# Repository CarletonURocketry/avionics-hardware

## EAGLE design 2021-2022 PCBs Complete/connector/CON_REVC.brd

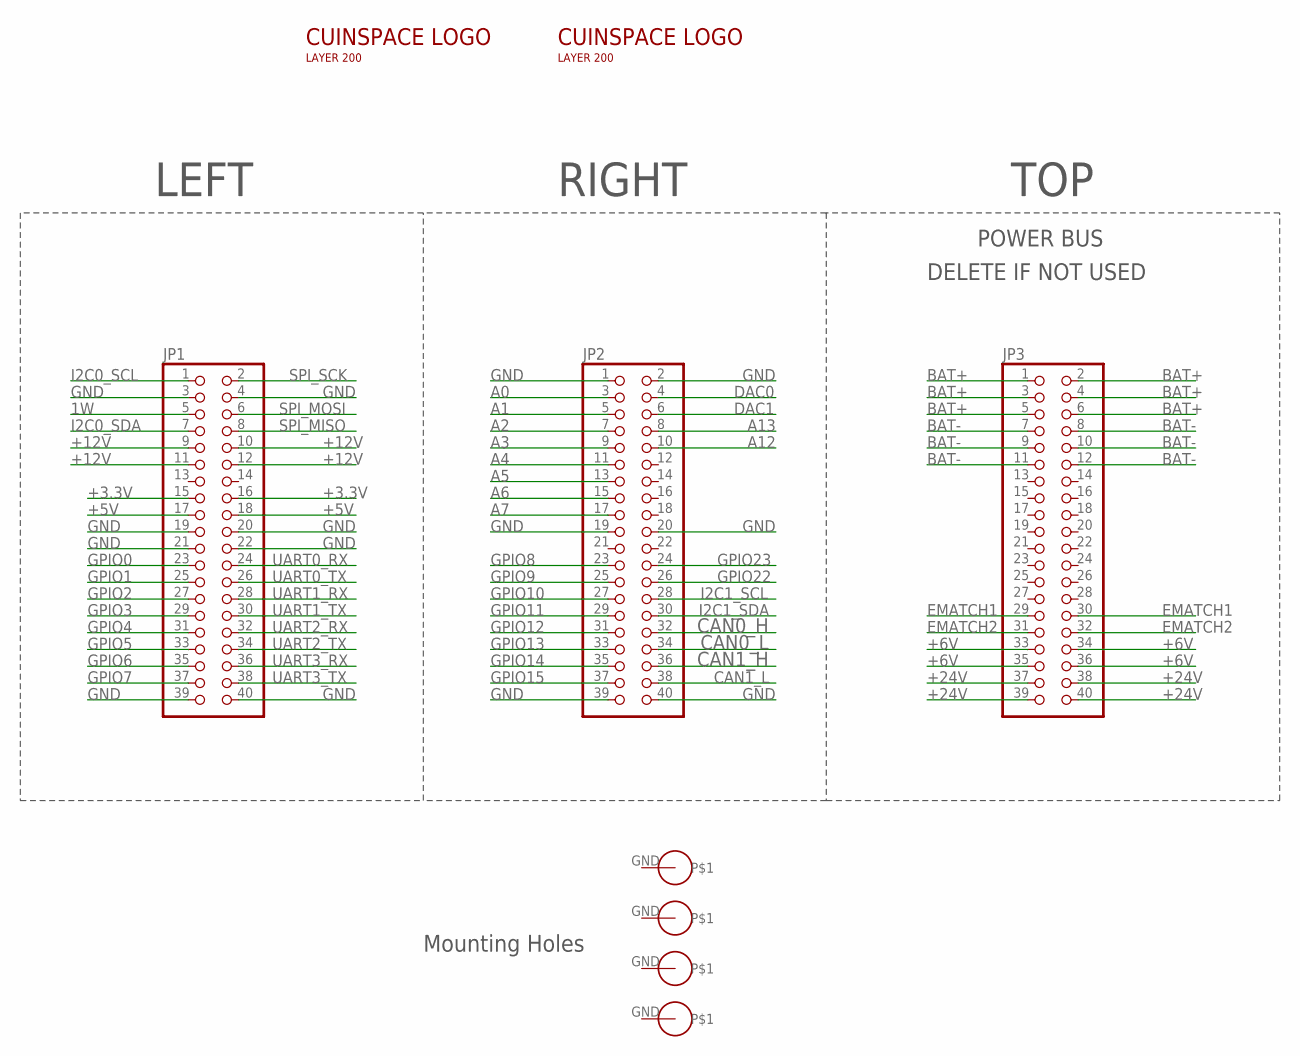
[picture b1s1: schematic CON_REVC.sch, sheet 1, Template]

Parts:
$$U$1: PS/104-MOUNTING-HOLE; PC/104-MOUNTING-HOLE
JP1, JP2, JP3: PINHD-2X20; 2X20
U$1, U$2, U$3: PS/104-MOUNTING-HOLE; PC/104-MOUNTING-HOLE
U$5, U$6: INSPACE3CM_L; INSPACE_3CM_LETTERS

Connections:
1W: JP1.5
+3.3V: JP1.15, JP1.16
+5V: JP1.17, JP1.18; also elsewhere on the board
+6V: JP3.33, JP3.34, JP3.35, JP3.36
+12V: JP1.9, JP1.10, JP1.11, JP1.12
+24V: JP3.37, JP3.38, JP3.39, JP3.40
A0: JP2.3
A1: JP2.5
A2: JP2.7
A3: JP2.9
A4: JP2.11
A5: JP2.13
A6: JP2.15
A7: JP2.17
A12: JP2.10
A13: JP2.8
BAT+: JP3.1, JP3.2, JP3.3, JP3.4, JP3.5, JP3.6; also elsewhere on the board
BAT-: JP3.7, JP3.8, JP3.9, JP3.10, JP3.11, JP3.12; also elsewhere on the board
CAN0_H: JP2.32; also elsewhere on the board
CAN0_L: JP2.34; also elsewhere on the board
CAN1_H: JP2.36; also elsewhere on the board
CAN1_L: JP2.38; also elsewhere on the board
DAC0: JP2.4
DAC1: JP2.6
EMATCH1: JP3.29, JP3.30; also elsewhere on the board
EMATCH2: JP3.31, JP3.32; also elsewhere on the board
GND: JP1.3, JP1.4, JP1.19, JP1.20, JP1.21, JP1.22, JP1.39, JP1.40, JP2.1, JP2.2, JP2.19, JP2.20, JP2.39, JP2.40; also elsewhere on the board
GPIO0: JP1.23
GPIO1: JP1.25
GPIO2: JP1.27
GPIO3: JP1.29
GPIO4: JP1.31
GPIO5: JP1.33
GPIO6: JP1.35
GPIO7: JP1.37
GPIO8: JP2.23
GPIO9: JP2.25
GPIO10: JP2.27
GPIO11: JP2.29
GPIO12: JP2.31
GPIO13: JP2.33
GPIO14: JP2.35
GPIO15: JP2.37; also elsewhere on the board
GPIO22: JP2.26
GPIO23: JP2.24
I2C0_SCL: JP1.1
I2C0_SDA: JP1.7
I2C1_SCL: JP2.28
I2C1_SDA: JP2.30
SPI_MISO: JP1.8
SPI_MOSI: JP1.6
SPI_SCK: JP1.2
UART0_RX: JP1.24
UART0_TX: JP1.26
UART1_RX: JP1.28
UART1_TX: JP1.30
UART2_RX: JP1.32
UART2_TX: JP1.34
UART3_RX: JP1.36
UART3_TX: JP1.38

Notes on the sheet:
POWER BUS
DELETE IF NOT USED
LEFT
RIGHT
TOP
Mounting Holes

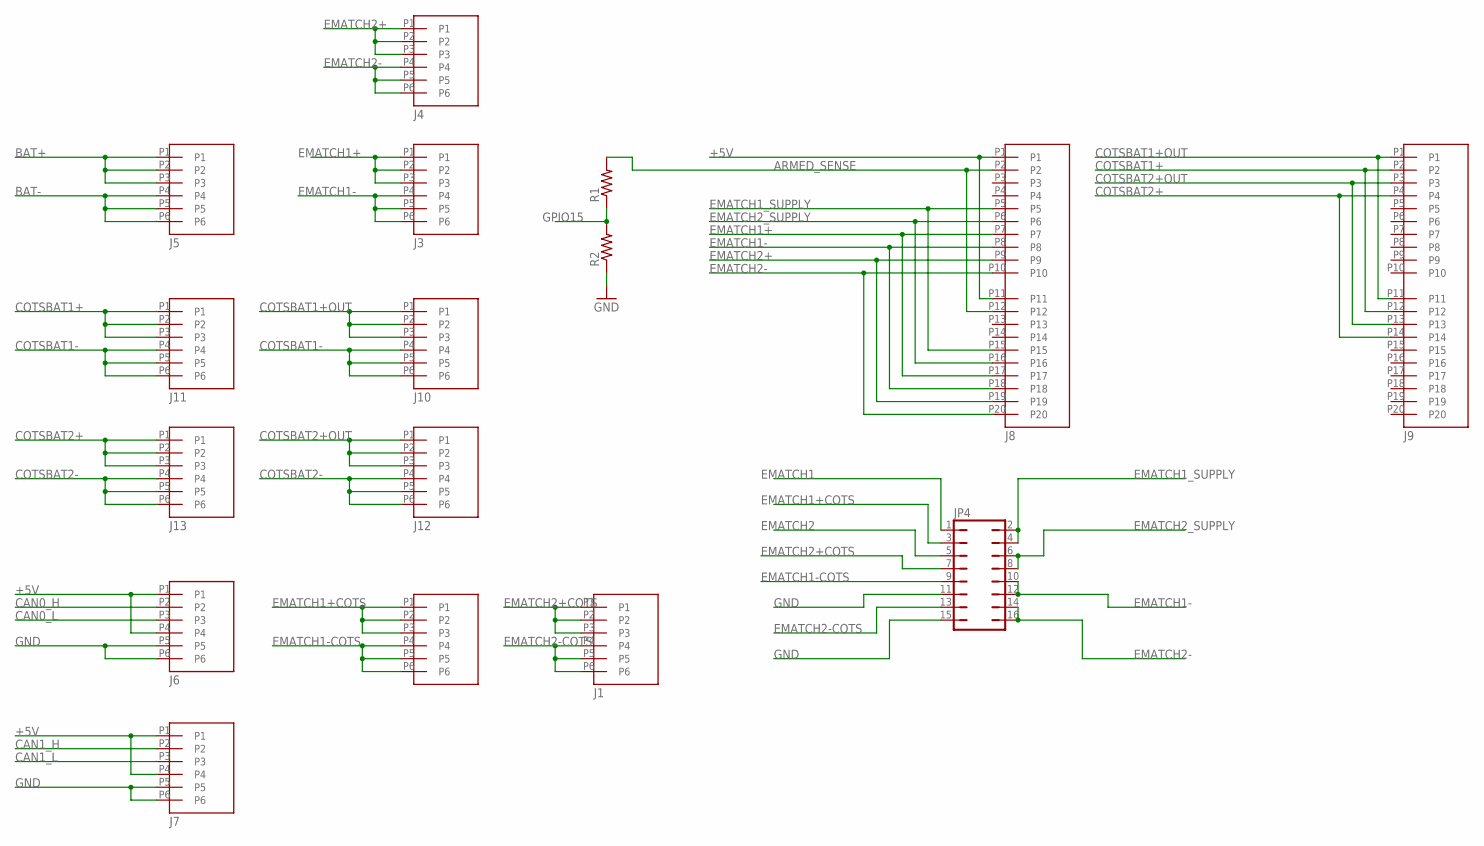
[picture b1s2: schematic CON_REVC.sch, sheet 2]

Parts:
J1, J2, J3, J4, J5, J6, J7, J10, J11, J12, J13: M80-5100642
J8, J9: M80-5102042
JP4: JP8Q
R1, R2: R-US_R0805; R0805

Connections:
+5V: J6.P1, J6.P4, J7.P1, J7.P4, J8.P1, J8.P11; also elsewhere on the board
ARMED_SENSE: J8.P2, J8.P12, R1.2
BAT+: J5.P1, J5.P2, J5.P3; also elsewhere on the board
BAT-: J5.P4, J5.P5, J5.P6; also elsewhere on the board
CAN0_H: J6.P2; also elsewhere on the board
CAN0_L: J6.P3; also elsewhere on the board
CAN1_H: J7.P2; also elsewhere on the board
CAN1_L: J7.P3; also elsewhere on the board
COTSBAT1+: J9.P2, J9.P12, J11.P1, J11.P2, J11.P3
COTSBAT1+OUT: J9.P1, J9.P11, J10.P1, J10.P2, J10.P3
COTSBAT1-: J10.P4, J10.P5, J10.P6, J11.P4, J11.P5, J11.P6
COTSBAT2+: J9.P4, J9.P14, J13.P1, J13.P2, J13.P3
COTSBAT2+OUT: J9.P3, J9.P13, J12.P1, J12.P2, J12.P3
COTSBAT2-: J12.P4, J12.P5, J12.P6, J13.P4, J13.P5, J13.P6
EMATCH1: JP4.1; also elsewhere on the board
EMATCH1+: J3.P1, J3.P2, J3.P3, J8.P7, J8.P17
EMATCH1+COTS: J2.P1, J2.P2, J2.P3, JP4.3
EMATCH1-: J3.P4, J3.P5, J3.P6, J8.P8, J8.P18, JP4.10, JP4.12
EMATCH1-COTS: J2.P4, J2.P5, J2.P6, JP4.9
EMATCH1_SUPPLY: J8.P5, J8.P15, JP4.2, JP4.4
EMATCH2: JP4.5; also elsewhere on the board
EMATCH2+: J4.P1, J4.P2, J4.P3, J8.P9, J8.P19
EMATCH2+COTS: J1.P1, J1.P2, J1.P3, JP4.7
EMATCH2-: J4.P4, J4.P5, J4.P6, J8.P10, J8.P20, JP4.14, JP4.16
EMATCH2-COTS: J1.P4, J1.P5, J1.P6, JP4.13
EMATCH2_SUPPLY: J8.P6, J8.P16, JP4.6, JP4.8
GND: J6.P5, J6.P6, J7.P5, J7.P6, JP4.11, JP4.15, R2.1; also elsewhere on the board
GPIO15: R1.1, R2.2; also elsewhere on the board

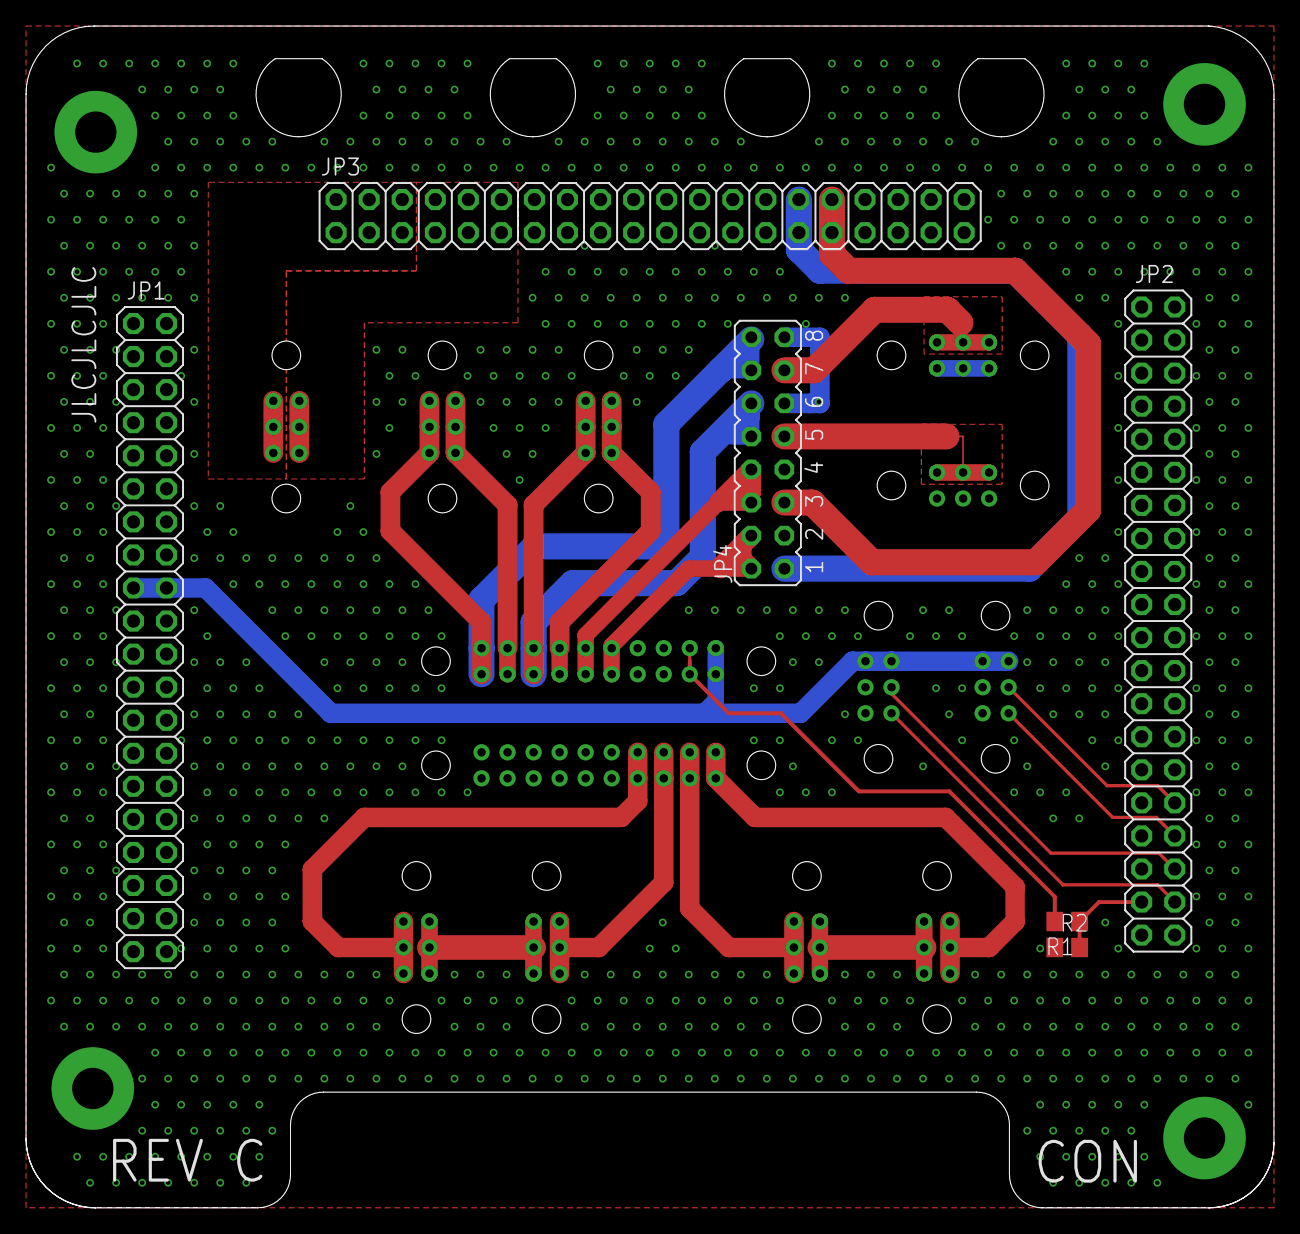
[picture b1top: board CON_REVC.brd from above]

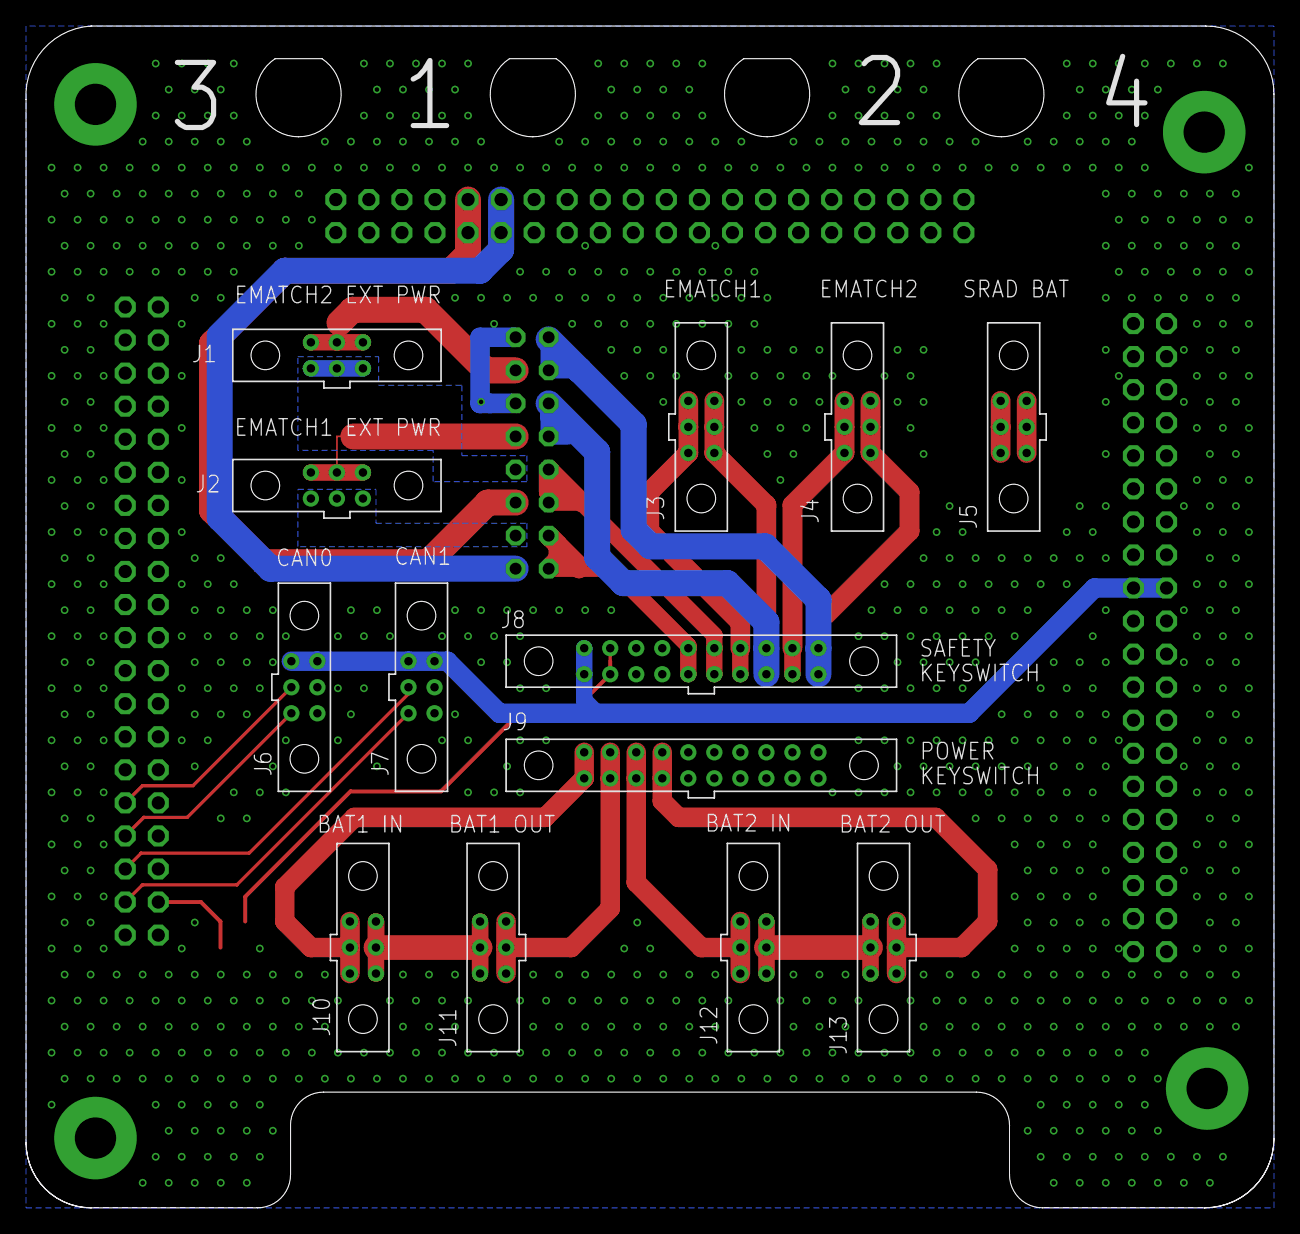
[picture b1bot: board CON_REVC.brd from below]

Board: 2 copper layers, 95.9 x 90.8 mm, 25 parts (15 on the bottom side), 32 nets.

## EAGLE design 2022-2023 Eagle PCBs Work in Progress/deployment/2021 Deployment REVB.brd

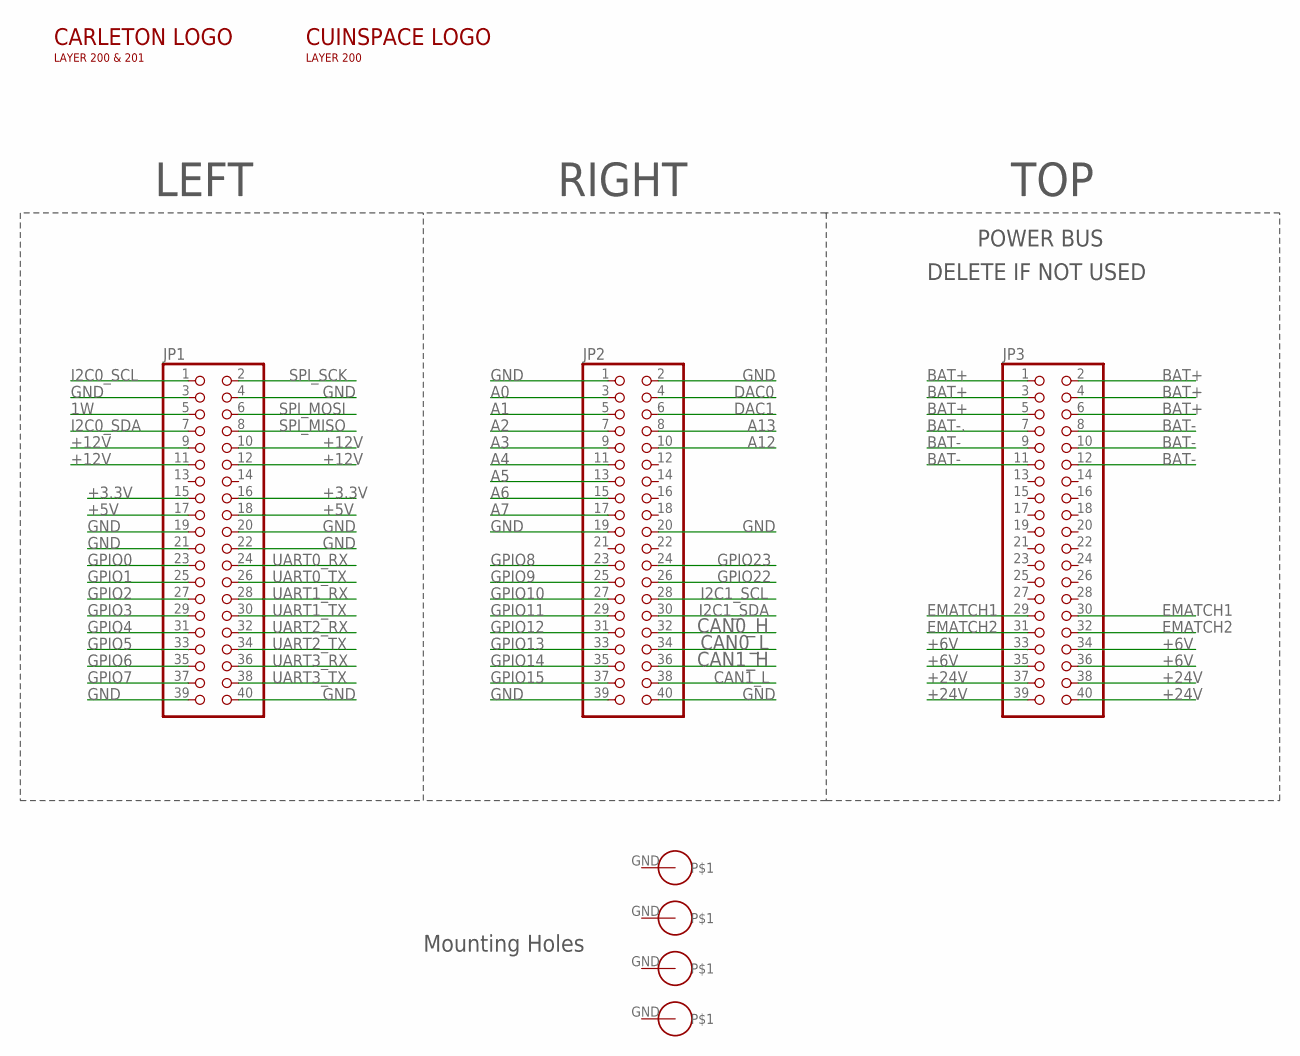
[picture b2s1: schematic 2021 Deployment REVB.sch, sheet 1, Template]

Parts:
$$U$1: PS/104-MOUNTING-HOLE; PC/104-MOUNTING-HOLE
JP1, JP2, JP3: PINHD-2X20; 2X20
U$1, U$2, U$3: PS/104-MOUNTING-HOLE; PC/104-MOUNTING-HOLE
U$4: CARLETON3CM; CARLETONU_3CM
U$6: INSPACE3CM_L; INSPACE_3CM_LETTERS

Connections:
1W: JP1.5
+3.3V: JP1.15, JP1.16
+5V: JP1.17, JP1.18
+6V: JP3.33, JP3.34, JP3.35, JP3.36
+12V: JP1.9, JP1.10, JP1.11, JP1.12
+24V: JP3.37, JP3.38, JP3.39, JP3.40
A0: JP2.3
A1: JP2.5
A2: JP2.7
A3: JP2.9
A4: JP2.11
A5: JP2.13
A6: JP2.15
A7: JP2.17
A12: JP2.10
A13: JP2.8
BAT+: JP3.1, JP3.2, JP3.3, JP3.4, JP3.5, JP3.6
BAT-: JP3.8, JP3.9, JP3.10, JP3.11, JP3.12
BAT-.: JP3.7
CAN0_H: JP2.32
CAN0_L: JP2.34
CAN1_H: JP2.36
CAN1_L: JP2.38
DAC0: JP2.4
DAC1: JP2.6
EMATCH1: JP3.29, JP3.30
EMATCH2: JP3.31, JP3.32
GND: JP1.3, JP1.4, JP1.19, JP1.20, JP1.21, JP1.22, JP1.39, JP1.40, JP2.1, JP2.2, JP2.19, JP2.20, JP2.39, JP2.40
GPIO0: JP1.23
GPIO1: JP1.25
GPIO2: JP1.27
GPIO3: JP1.29
GPIO4: JP1.31
GPIO5: JP1.33
GPIO6: JP1.35
GPIO7: JP1.37
GPIO8: JP2.23
GPIO9: JP2.25
GPIO10: JP2.27
GPIO11: JP2.29
GPIO12: JP2.31
GPIO13: JP2.33
GPIO14: JP2.35
GPIO15: JP2.37
GPIO22: JP2.26
GPIO23: JP2.24
I2C0_SCL: JP1.1
I2C0_SDA: JP1.7
I2C1_SCL: JP2.28
I2C1_SDA: JP2.30
SPI_MISO: JP1.8
SPI_MOSI: JP1.6
SPI_SCK: JP1.2
UART0_RX: JP1.24
UART0_TX: JP1.26
UART1_RX: JP1.28
UART1_TX: JP1.30
UART2_RX: JP1.32
UART2_TX: JP1.34
UART3_RX: JP1.36
UART3_TX: JP1.38

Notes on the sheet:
POWER BUS
DELETE IF NOT USED
LEFT
RIGHT
TOP
Mounting Holes

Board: 2 copper layers, 9 parts (0 on the bottom side), 10 nets, no tracks yet.

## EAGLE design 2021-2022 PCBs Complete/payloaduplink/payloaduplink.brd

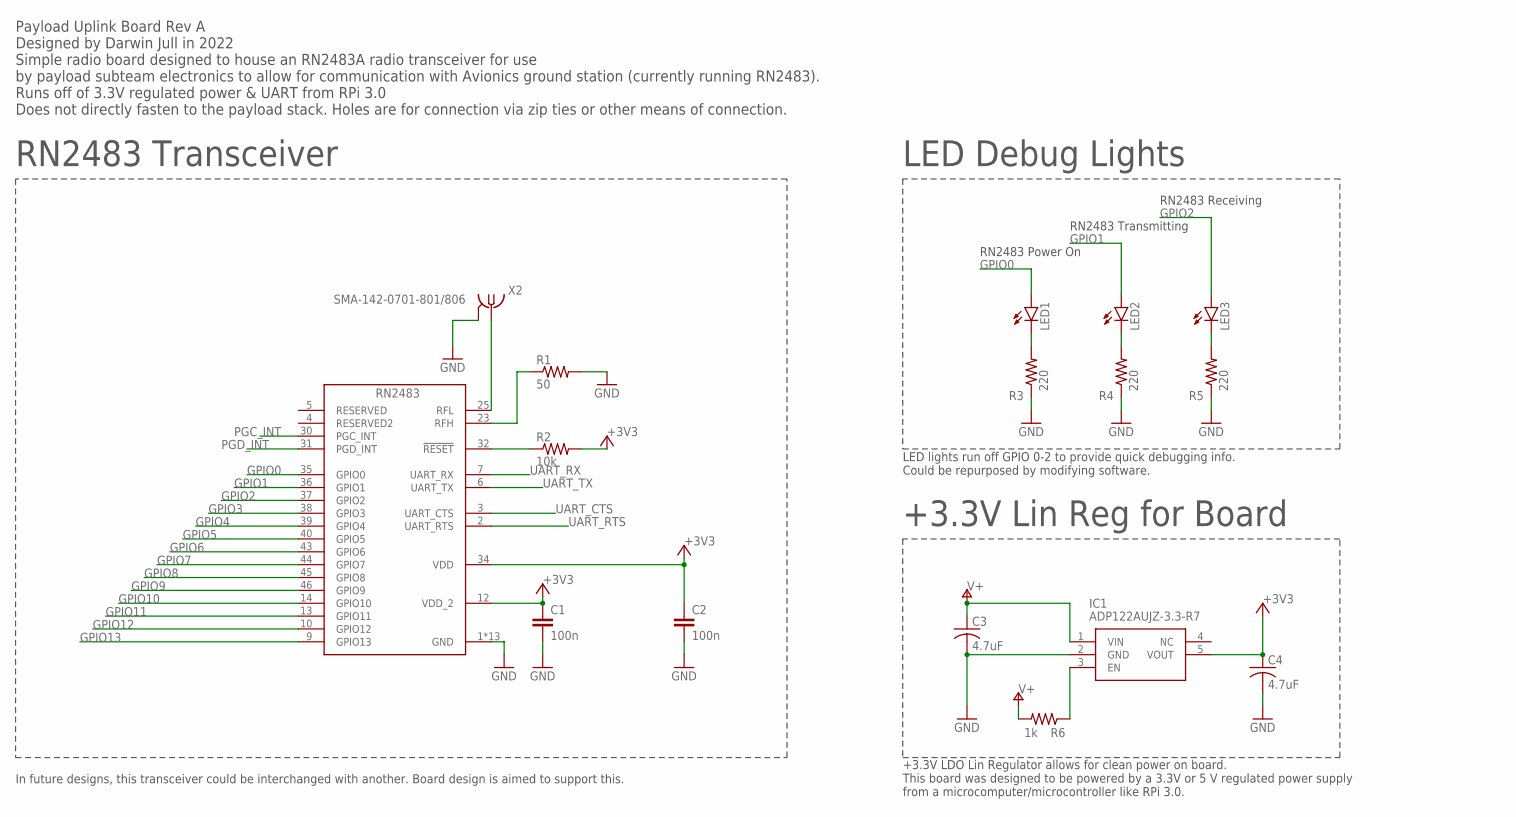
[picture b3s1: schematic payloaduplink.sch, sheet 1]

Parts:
C1, C2: 100n; C0805
C3, C4: 4.7uF; C0805
IC1: ADP122AUJZ-3.3-R7; SOT95P280X100-5N
LED1, LED2, LED3: LEDCHIPLED_0603; CHIPLED_0603
R1: 50; R0402
R2: 10k; R0805
R3, R4, R5: 220; R0805
R6: 1k; R0805
U$1: RN2483_TRANSCIEVER; RN2483
X2: SMA-142-0701-801/806; J502-ND-142-0701-801/806

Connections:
+3V3: C1.1, C2.1, C4.1, IC1.5 (VOUT), R2.2, U$1.12 (VDD_2), U$1.34 (VDD)
GND: C1.2, C2.2, C3.2, C4.2, IC1.2 (GND), R1.2, R3.1, R4.1, R5.1, U$1.1 (GND), U$1.8 (GND), U$1.11 (GND), U$1.20 (GND), U$1.21 (GND), U$1.22 (GND), U$1.24 (GND), U$1.26 (GND), U$1.27 (GND), U$1.28 (GND), U$1.33 (GND), U$1.41 (GND), U$1.47 (GND), X2.G@1 (2), X2.G@2 (2), X2.G@3 (2), X2.G@4 (2); also elsewhere on the board
GPIO0: LED1.A, U$1.35 (GPIO0)
GPIO1: LED2.A, U$1.36 (GPIO1)
GPIO2: LED3.A, U$1.37 (GPIO2)
GPIO3: U$1.38 (GPIO3); also elsewhere on the board
GPIO4: U$1.39 (GPIO4); also elsewhere on the board
GPIO5: U$1.40 (GPIO5); also elsewhere on the board
GPIO6: U$1.43 (GPIO6); also elsewhere on the board
GPIO7: U$1.44 (GPIO7); also elsewhere on the board
GPIO8: U$1.45 (GPIO8); also elsewhere on the board
GPIO9: U$1.46 (GPIO9); also elsewhere on the board
GPIO10: U$1.14 (GPIO10); also elsewhere on the board
GPIO11: U$1.13 (GPIO11); also elsewhere on the board
GPIO12: U$1.10 (GPIO12); also elsewhere on the board
GPIO13: U$1.9 (GPIO13); also elsewhere on the board
unnamed: U$1.25 (RFL), X2.1
unnamed: R1.1, U$1.23 (RFH)
unnamed: LED1.C, R3.2
unnamed: LED2.C, R4.2
unnamed: LED3.C, R5.2
unnamed: R2.1, U$1.32 (!RESET)
unnamed: IC1.3 (EN), R6.1
PGC_INT: U$1.30 (PGC_INT); also elsewhere on the board
PGD_INT: U$1.31 (PGD_INT); also elsewhere on the board
UART_CTS: U$1.3 (UART_CTS); also elsewhere on the board
UART_RTS: U$1.2 (UART_RTS); also elsewhere on the board
UART_RX: U$1.7 (UART_RX); also elsewhere on the board
UART_TX: U$1.6 (UART_TX); also elsewhere on the board
V+: C3.1, IC1.1 (VIN), R6.2; also elsewhere on the board

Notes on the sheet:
RN2483 Transceiver
LED Debug Lights
+3.3V Lin Reg for Board
In future designs, this transceiver could be interchanged with another. Board design is aimed to support this.
+3.3V LDO Lin Regulator allows for clean power on board. This board was designed to be powered by a 3.3V or 5 V regulated power supply from a microcomputer/microcontroller like RPi 3.0.
LED lights run off GPIO 0-2 to provide quick debugging info. Could be repurposed by modifying software.
Payload Uplink Board Rev A Designed by Darwin Jull in 2022 Simple radio board designed to house an RN2483A radio transceiver for use by payload subteam electronics to allow for communication with Avionics ground station (currently running RN2483). Runs off of 3.3V regulated power & UART from RPi 3.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
RN2483 Power On
RN2483 Transmitting
RN2483 Receiving

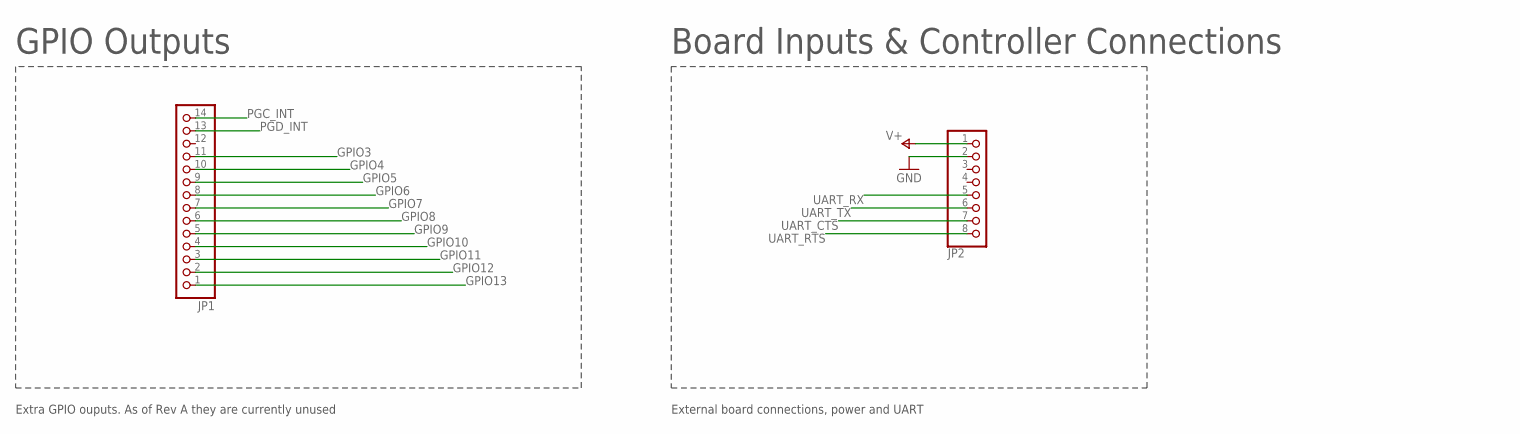
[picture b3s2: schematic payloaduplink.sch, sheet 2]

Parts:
JP1: PINHD-1X14; 1X14
JP2: PINHD-1X8; 1X08

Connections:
GND: JP2.2; also elsewhere on the board
GPIO3: JP1.11; also elsewhere on the board
GPIO4: JP1.10; also elsewhere on the board
GPIO5: JP1.9; also elsewhere on the board
GPIO6: JP1.8; also elsewhere on the board
GPIO7: JP1.7; also elsewhere on the board
GPIO8: JP1.6; also elsewhere on the board
GPIO9: JP1.5; also elsewhere on the board
GPIO10: JP1.4; also elsewhere on the board
GPIO11: JP1.3; also elsewhere on the board
GPIO12: JP1.2; also elsewhere on the board
GPIO13: JP1.1; also elsewhere on the board
PGC_INT: JP1.14; also elsewhere on the board
PGD_INT: JP1.13; also elsewhere on the board
UART_CTS: JP2.7; also elsewhere on the board
UART_RTS: JP2.8; also elsewhere on the board
UART_RX: JP2.5; also elsewhere on the board
UART_TX: JP2.6; also elsewhere on the board
V+: JP2.1; also elsewhere on the board

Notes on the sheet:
GPIO Outputs
Board Inputs & Controller Connections
External board connections, power and UART
Extra GPIO ouputs. As of Rev A they are currently unused

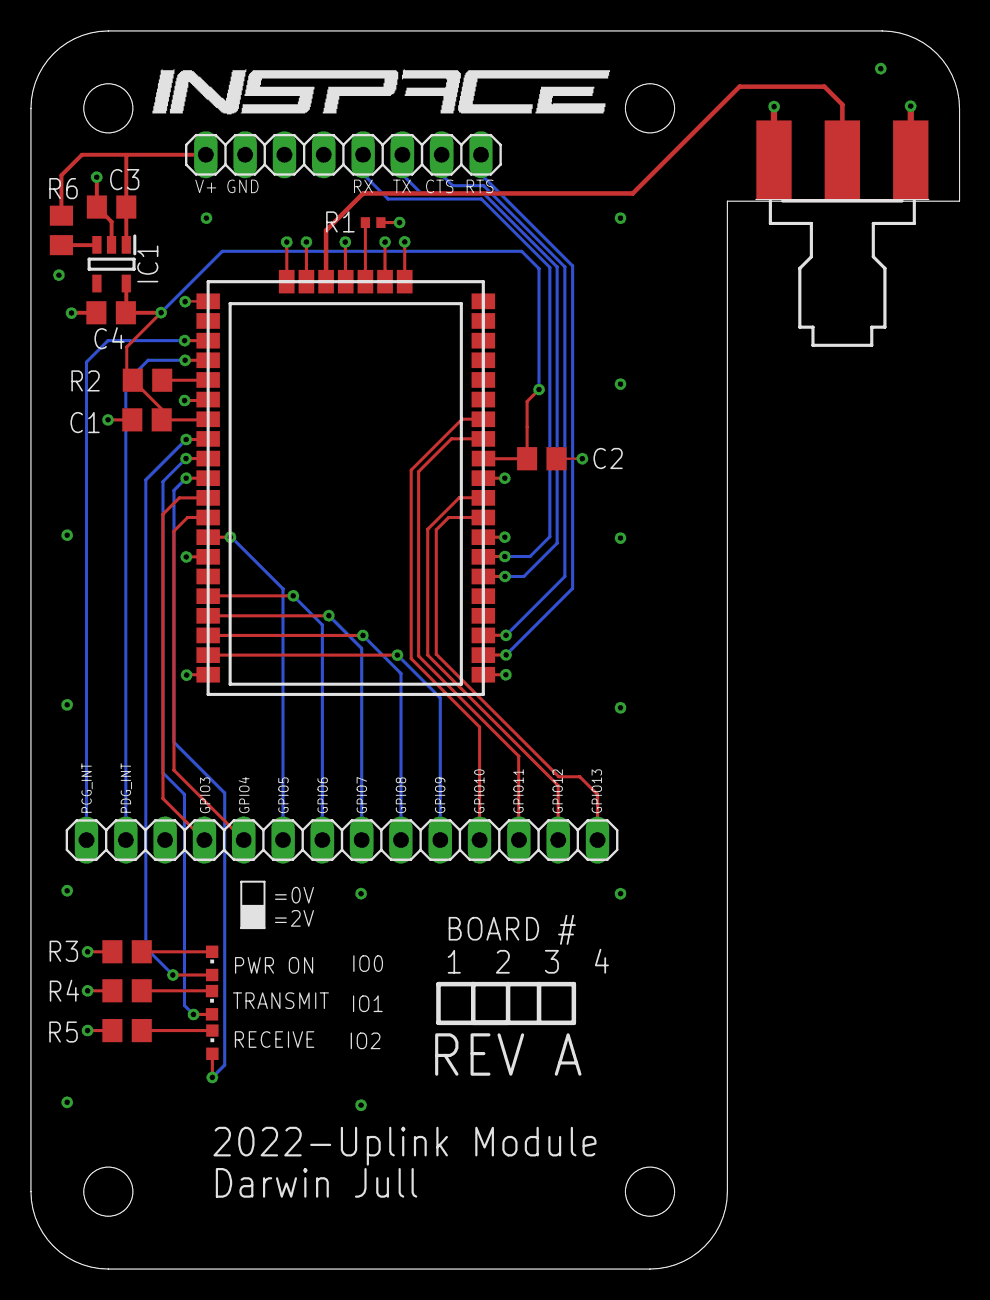
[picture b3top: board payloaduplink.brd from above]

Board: 4 copper layers, 60.0 x 80.0 mm, 19 parts (0 on the bottom side), 30 nets.

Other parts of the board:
U$2: INSPACE_3CM_LETTERS

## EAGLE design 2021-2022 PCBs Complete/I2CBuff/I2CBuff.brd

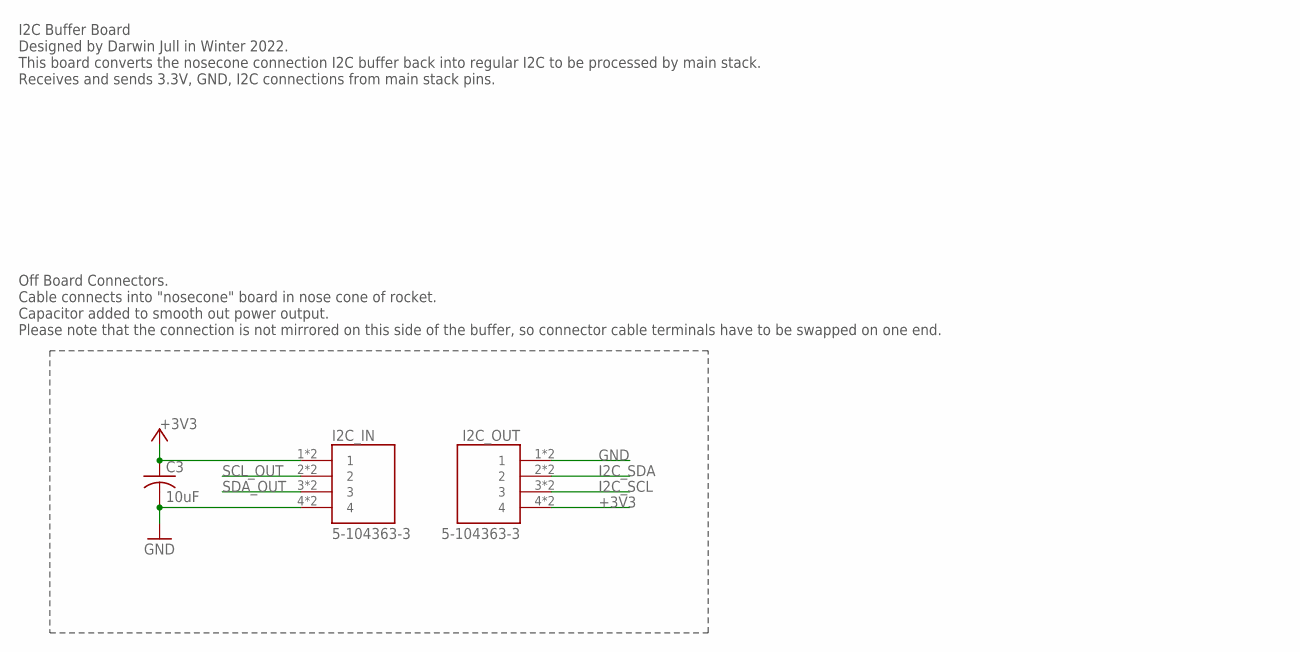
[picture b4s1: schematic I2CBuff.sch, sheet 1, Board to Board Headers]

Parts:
C3: 10uF; C0805
I2C_IN, I2C_OUT: 5-104363-3; TE_5-104363-3

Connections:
+3V3: C3.1, I2C_IN.1, I2C_IN.1_1 (1), I2C_OUT.4, I2C_OUT.4_1 (4); also elsewhere on the board
GND: C3.2, I2C_IN.4, I2C_IN.4_1 (4), I2C_OUT.1, I2C_OUT.1_1 (1); also elsewhere on the board
I2C_SCL: I2C_OUT.3, I2C_OUT.3_1 (3); also elsewhere on the board
I2C_SDA: I2C_OUT.2, I2C_OUT.2_1 (2); also elsewhere on the board
SCL_OUT: I2C_IN.2, I2C_IN.2_1 (2); also elsewhere on the board
SDA_OUT: I2C_IN.3, I2C_IN.3_1 (3); also elsewhere on the board

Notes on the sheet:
I2C Buffer Board Designed by Darwin Jull in Winter 2022. This board converts the nosecone connection I2C buffer back into regular I2C to be processed by main stack. Receives and sends 3.3V, GND, I2C connections from main stack pins.
Off Board Connectors. Cable connects into "nosecone" board in nose cone of rocket. Capacitor added to smooth out power output. Please note that the connection is not mirrored on this side of the buffer, so connector cable terminals have to be swapped on one end.

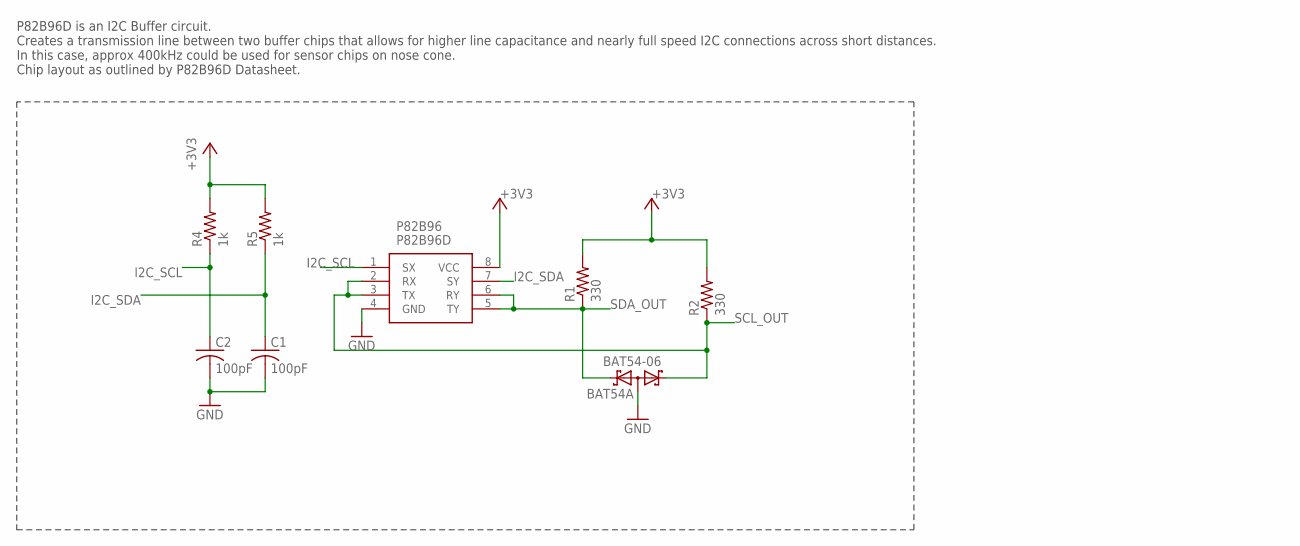
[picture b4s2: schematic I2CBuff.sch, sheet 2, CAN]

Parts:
C1, C2: 100pF; C0805
D1: BAT54-06; SOT23
P82B96: P82B96D; SOIC127P600X175-8N
R1, R2: 330; R0805
R4, R5: 1k; R0805

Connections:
+3V3: P82B96.8 (VCC), R1.2, R2.2, R4.2, R5.2; also elsewhere on the board
GND: C1.2, C2.2, D1.3, P82B96.4 (GND); also elsewhere on the board
I2C_SCL: C2.1, P82B96.1 (SX), R4.1; also elsewhere on the board
I2C_SDA: C1.1, P82B96.7 (SY), R5.1; also elsewhere on the board
SCL_OUT: D1.1, P82B96.2 (RX), P82B96.3 (TX), R2.1; also elsewhere on the board
SDA_OUT: D1.2, P82B96.5 (TY), P82B96.6 (RY), R1.1; also elsewhere on the board

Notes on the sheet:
P82B96D is an I2C Buffer circuit. Creates a transmission line between two buffer chips that allows for higher line capacitance and nearly full speed I2C connections across short distances. In this case, approx 400kHz could be used for sensor chips on nose cone. Chip layout as outlined by P82B96D Da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

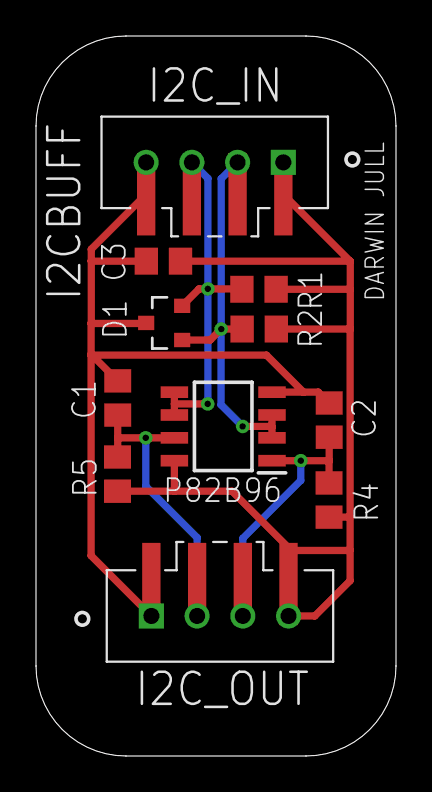
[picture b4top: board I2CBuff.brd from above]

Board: 2 copper layers, 20.0 x 40.0 mm, 11 parts (0 on the bottom side), 6 nets.

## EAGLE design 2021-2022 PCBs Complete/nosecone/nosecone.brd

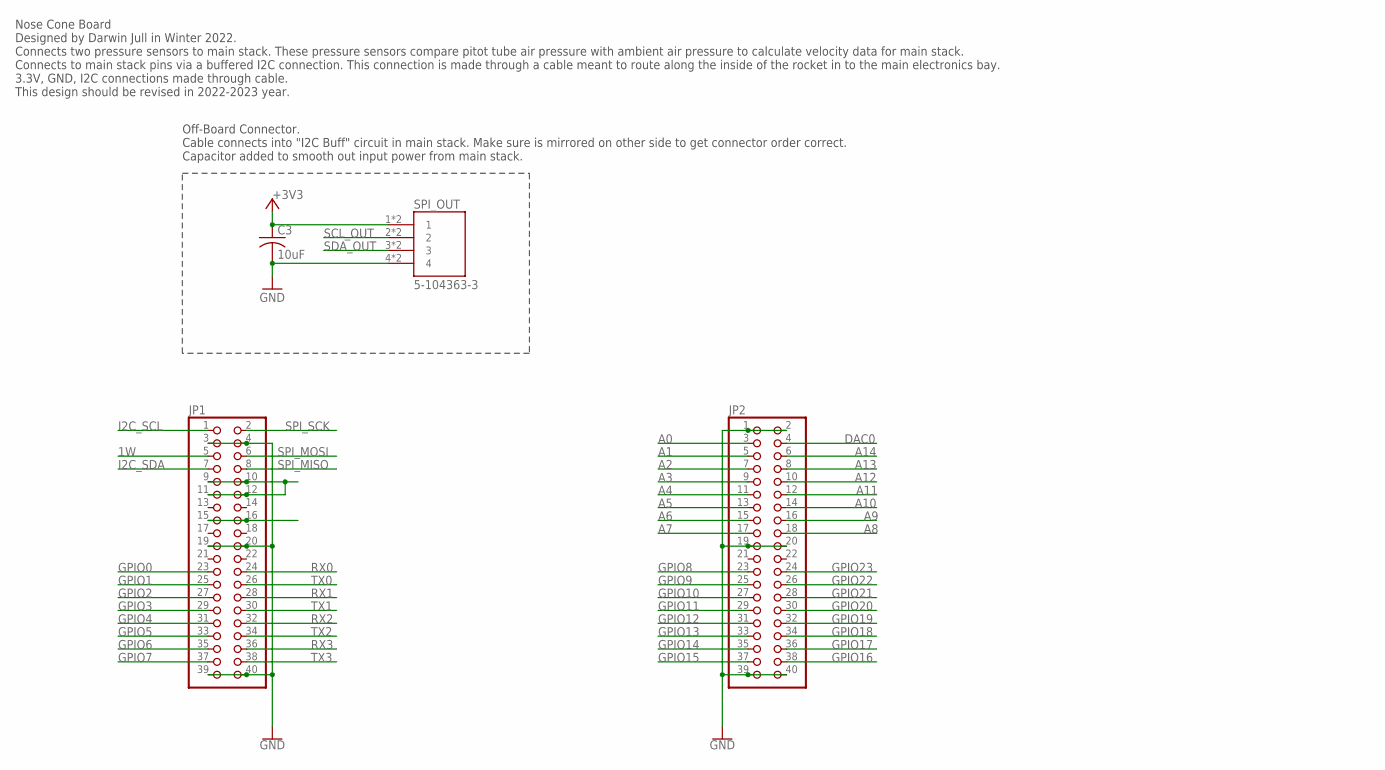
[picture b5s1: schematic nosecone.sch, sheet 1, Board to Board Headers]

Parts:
C3: 10uF; C0805
JP1, JP2: PINHD-2X20; 2X20
SPI_OUT: 5-104363-3; TE_5-104363-3

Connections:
1W: JP1.5
+3V3: C3.1, SPI_OUT.1, SPI_OUT.1_1 (1); also elsewhere on the board
A0: JP2.3
A1: JP2.5
A2: JP2.7
A3: JP2.9
A4: JP2.11
A5: JP2.13
A6: JP2.15
A7: JP2.17
A8: JP2.18
A9: JP2.16
A10: JP2.14
A11: JP2.12
A12: JP2.10
A13: JP2.8
A14: JP2.6
DAC0: JP2.4
GND: C3.2, JP1.3, JP1.4, JP1.19, JP1.20, JP1.39, JP1.40, JP2.1, JP2.2, JP2.19, JP2.20, JP2.39, JP2.40, SPI_OUT.4, SPI_OUT.4_1 (4); also elsewhere on the board
GPIO0: JP1.23
GPIO1: JP1.25
GPIO2: JP1.27
GPIO3: JP1.29
GPIO4: JP1.31
GPIO5: JP1.33
GPIO6: JP1.35
GPIO7: JP1.37
GPIO8: JP2.23
GPIO9: JP2.25
GPIO10: JP2.27
GPIO11: JP2.29
GPIO12: JP2.31
GPIO13: JP2.33
GPIO14: JP2.35
GPIO15: JP2.37
GPIO16: JP2.38
GPIO17: JP2.36
GPIO18: JP2.34
GPIO19: JP2.32
GPIO20: JP2.30
GPIO21: JP2.28
GPIO22: JP2.26
GPIO23: JP2.24
I2C_SCL: JP1.1; also elsewhere on the board
I2C_SDA: JP1.7; also elsewhere on the board
unnamed: JP1.9, JP1.10, JP1.11, JP1.12
unnamed: JP1.15, JP1.16
RX0: JP1.24
RX1: JP1.28
RX2: JP1.32
RX3: JP1.36
SCL_OUT: SPI_OUT.2, SPI_OUT.2_1 (2); also elsewhere on the board
SDA_OUT: SPI_OUT.3, SPI_OUT.3_1 (3); also elsewhere on the board
SPI_MISO: JP1.8
SPI_MOSI: JP1.6
SPI_SCK: JP1.2
TX0: JP1.26
TX1: JP1.30
TX2: JP1.34
TX3: JP1.38

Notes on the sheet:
Off-Board Connector. Cable connects into "I2C Buff" circuit in main stack. Make sure is mirrored on other side to get connector order correct. Capacitor added to smooth out input power from main stack.
Nose Cone Board Designed by Darwin Jull in Winter 2022. Connects two pressure sensors to main stack. These pressure sensors compare pitot tube air pressure with ambient air pressure to calculate velocity data for main stack. Connects to main stack pins via a buffered I2C connection. This connection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

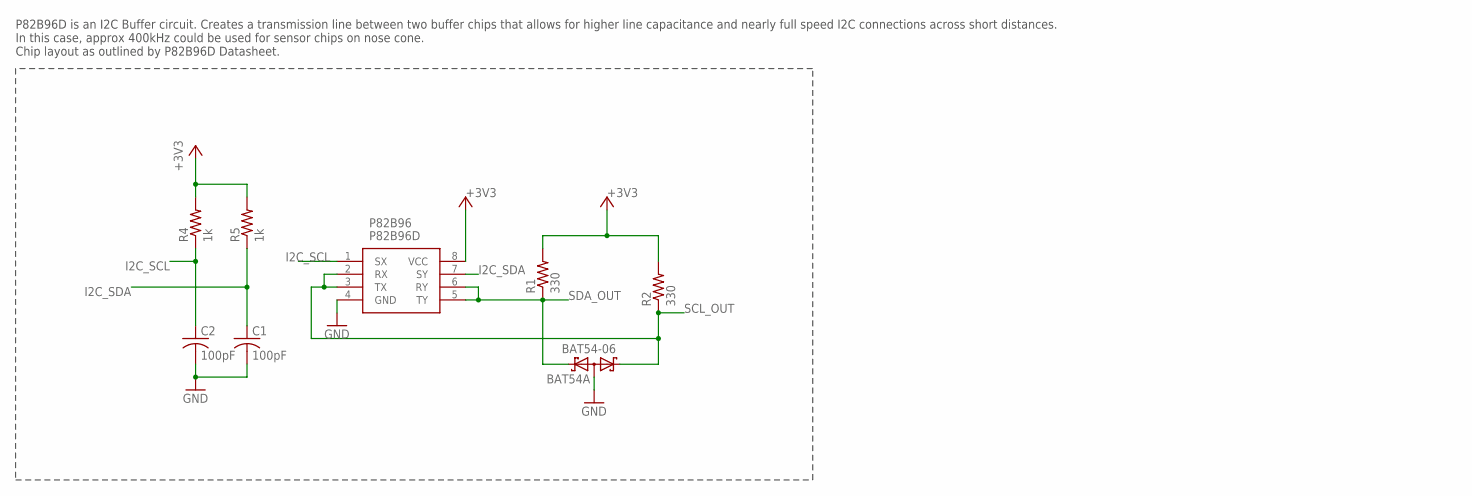
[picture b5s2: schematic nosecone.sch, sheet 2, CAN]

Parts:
C1, C2: 100pF; C0805
D1: BAT54-06; SOT23
P82B96: P82B96D; SOIC127P600X175-8N
R1, R2: 330; R0805
R4, R5: 1k; R0805

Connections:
+3V3: P82B96.8 (VCC), R1.2, R2.2, R4.2, R5.2; also elsewhere on the board
GND: C1.2, C2.2, D1.3, P82B96.4 (GND); also elsewhere on the board
I2C_SCL: C2.1, P82B96.1 (SX), R4.1; also elsewhere on the board
I2C_SDA: C1.1, P82B96.7 (SY), R5.1; also elsewhere on the board
SCL_OUT: D1.1, P82B96.2 (RX), P82B96.3 (TX), R2.1; also elsewhere on the board
SDA_OUT: D1.2, P82B96.5 (TY), P82B96.6 (RY), R1.1; also elsewhere on the board

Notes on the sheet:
P82B96D is an I2C Buffer circuit. Creates a transmission line between two buffer chips that allows for higher line capacitance and nearly full speed I2C connections across short distances. In this case, approx 400kHz could be used for sensor chips on nose cone. Chip layout as outlined by P82B96D Da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

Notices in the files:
parts and their libraries:
SparkFun-PowerSymbols: Licensing: Creative Commons ShareAlike 4.0 International - https://creativecommons.org/licenses/by-sa/4.0
